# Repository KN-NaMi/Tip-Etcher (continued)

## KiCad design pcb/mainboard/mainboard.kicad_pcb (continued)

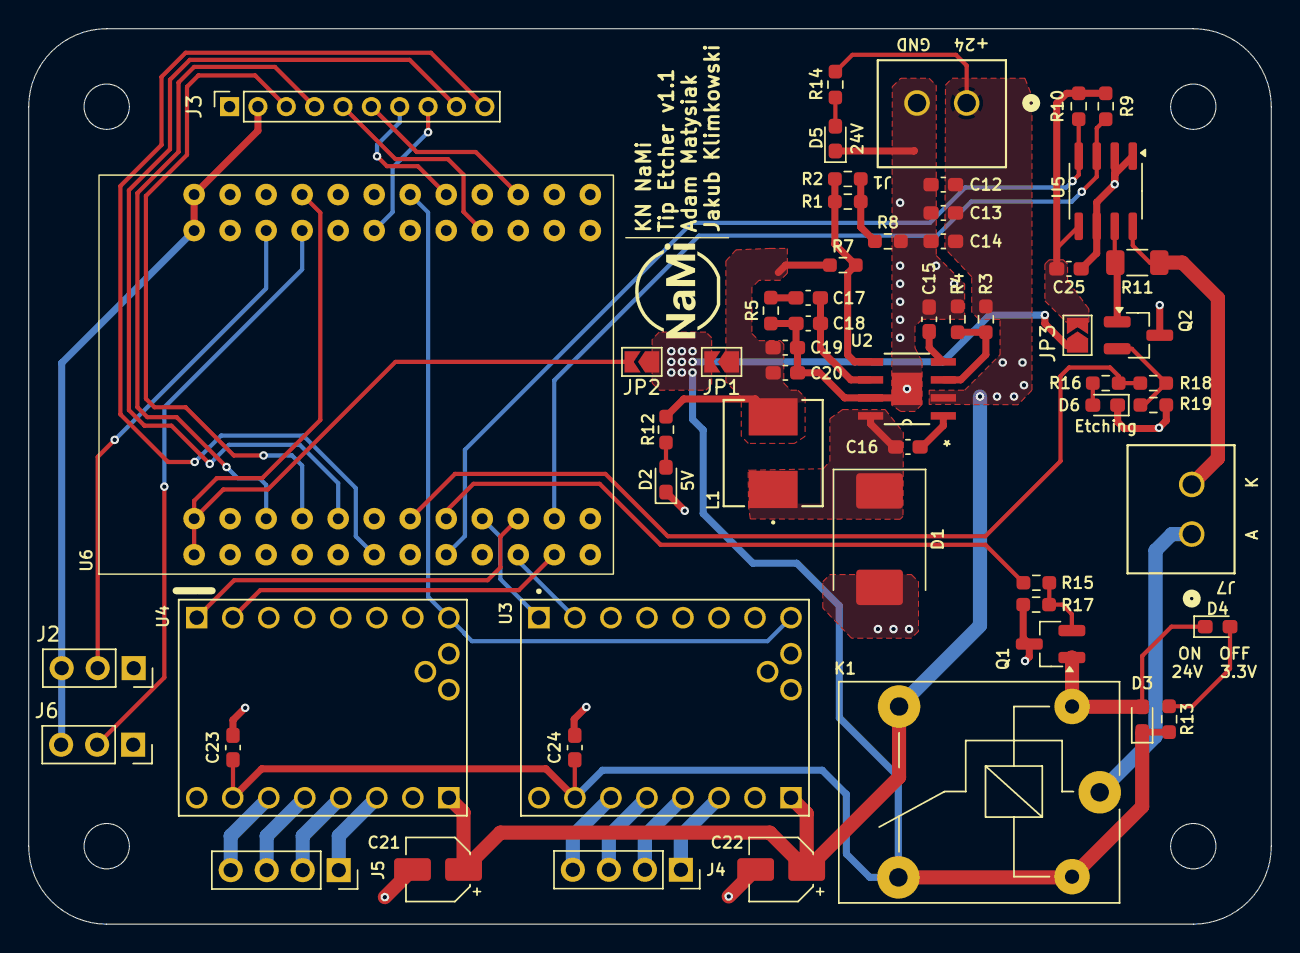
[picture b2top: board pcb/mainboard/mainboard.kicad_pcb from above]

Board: 2 copper layers, 87.6 x 63.1 mm, 61 parts (0 on the bottom side), 52 nets.

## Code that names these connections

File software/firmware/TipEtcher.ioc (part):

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Mcu.Name=STM32G474C(B-C-E)Ux
Mcu.Package=UFQFPN48
Mcu.UserName=STM32G474CEUx
PA0.GPIOParameters=GPIO_Label
PA0.GPIO_Label=OLED_RESET
PA0.Signal=GPIO_Output
PA1.GPIOParameters=GPIO_Label
PA1.GPIO_Label=OLED_DC
PA1.Signal=GPIO_Output
PA12.GPIOParameters=GPIO_Label
PA12.GPIO_Label=TIP_EN
PA12.Signal=GPIO_Output
PA15.Mode=I2C
PA15.Signal=I2C1_SCL
PA4.GPIOParameters=GPIO_Label
PA4.GPIO_Label=OLED_CS
PA4.Signal=GPIO_Output
PA6.GPIOParameters=GPIO_Label
PA6.GPIO_Label=M_ENABLE
PA6.Signal=GPIO_Output
PA7.GPIOParameters=GPIO_Label,GPIO_ModeDefaultEXTI
PA7.GPIO_Label=ENCODER_BTN
PA7.GPIO_ModeDefaultEXTI=GPIO_MODE_IT_FALLING
PA7.Signal=GPXTI7
PA8.GPIOParameters=GPIO_Label,GPIO_ModeDefaultEXTI
PA8.GPIO_Label=ENCODER_SIGA
PA8.GPIO_ModeDefaultEXTI=GPIO_MODE_IT_RISING_FALLING
PA8.Signal=GPXTI8
PA9.GPIOParameters=GPIO_Label
PA9.GPIO_Label=ENCODER_SIGB
PA9.Signal=GPIO_Input
PB10.GPIOParameters=GPIO_Label
PB10.GPIO_Label=LIMIT_SWITCH_1
PB10.Signal=GPIO_Input
PB13.GPIOParameters=GPIO_Label
PB13.GPIO_Label=OLED_SPI2_SCK
PB13.Mode=TX_Only_Simplex_Unidirect_Master
PB13.Signal=SPI2_SCK
PB15.GPIOParameters=GPIO_Label
PB15.GPIO_Label=OLED_SPI2_MOSI
PB15.Mode=TX_Only_Simplex_Unidirect_Master
PB15.Signal=SPI2_MOSI
PB3.GPIOParameters=GPIO_Label
PB3.GPIO_Label=DIR_1
PB3.Signal=GPIO_Output
PB4.GPIOParameters=GPIO_Label
PB4.GPIO_Label=STEP_1
PB4.Signal=GPIO_Output
PB5.GPIOParameters=GPIO_Label
PB5.GPIO_Label=DIR_2
PB5.Signal=GPIO_Output
PB6.GPIOParameters=GPIO_Label
PB6.GPIO_Label=STEP_2
PB6.Signal=GPIO_Output
PB7.Mode=I2C
PB7.Signal=I2C1_SDA
PC10.GPIOParameters=GPIO_Label
PC10.GPIO_Label=V_SELECT
PC10.Signal=GPIO_Output
PC13.GPIOParameters=GPIO_Label
PC13.GPIO_Label=BOARD_BTN
PC13.Signal=GPIO_Input
PC6.GPIOParameters=GPIO_Label
PC6.GPIO_Label=LED
PC6.Signal=GPIO_Output
RCC.HSE_VALUE=8000000
RCC.SYSCLKFreq_VALUE=16000000
board=custom

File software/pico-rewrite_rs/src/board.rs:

use embedded_hal::digital::OutputPin;

use crate::hal;

#[derive(Clone, Copy, Debug, Eq, PartialEq)]
#[repr(u8)]
pub enum GpioPin {
    Gpio0,
    Gpio1,
    Gpio2,
    Gpio3,
    Gpio4,
    Gpio5,
    Gpio6,
    Gpio7,
    Gpio8,
    Gpio9,
    Gpio10,
    Gpio11,
    Gpio12,
    Gpio13,
    Gpio14,
    Gpio15,
    Gpio16,
    Gpio17,
    Gpio18,
    Gpio19,
    Gpio20,
    Gpio21,
    Gpio22,
    Gpio23,
    Gpio24,
    Gpio25,
    Gpio26,
    Gpio27,
    Gpio28,
    Gpio29,
}

#[derive(Clone, Copy, Debug, Default)]
pub struct PinMap {
    pub board_button: Option<GpioPin>,
    pub oled_reset: Option<GpioPin>,
    pub oled_data_command: Option<GpioPin>,
    pub oled_chip_select: Option<GpioPin>,
    pub motor_enable: Option<GpioPin>,
    pub encoder_button: Option<GpioPin>,
    pub limit_switch_1: Option<GpioPin>,
    pub oled_spi_clock: Option<GpioPin>,
    pub oled_spi_data: Option<GpioPin>,
    pub status_led: Option<GpioPin>,
    pub encoder_a: Option<GpioPin>,
    pub encoder_b: Option<GpioPin>,
    pub tip_enable: Option<GpioPin>,
    pub voltage_select: Option<GpioPin>,
    pub motor_1_direction: Option<GpioPin>,
    pub motor_1_step: Option<GpioPin>,
    pub motor_2_direction: Option<GpioPin>,
    pub motor_2_step: Option<GpioPin>,
    pub current_sensor_i2c_clock: Option<GpioPin>,
    pub current_sensor_i2c_data: Option<GpioPin>,
}

// Assign RP GPIOs here after the target Pico board and pinout are chosen.
pub const PIN_MAP: PinMap = PinMap {
    board_button: None,
    oled_reset: None,
    oled_data_command: None,
    oled_chip_select: None,
    motor_enable: None,
    encoder_button: None,
    limit_switch_1: None,
    oled_spi_clock: None,
    oled_spi_data: None,
    status_led: None,
    encoder_a: None,
    encoder_b: None,
    tip_enable: None,
    voltage_select: None,
    motor_1_direction: None,
    motor_1_step: None,
    motor_2_direction: None,
    motor_2_step: None,
    current_sensor_i2c_clock: None,
    current_sensor_i2c_data: None,
};

pub struct BlinkyPins<LedPin> {
    pub led: LedPin,
}


//OLED: CS(port, pin), DC(port, pin), RESET(port, pin), 
//ENCODER: SIGA(port, pin), SIGB(port, pin), BTN(port, pin) 
pub struct MENU; 

pub fn configure_blinky(pins: hal::gpio::Pins) -> BlinkyPins<impl OutputPin> {
    BlinkyPins {
        led: pins.gpio25.into_push_pull_output(),
    }
}

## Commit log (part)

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2025-02-09 init
2025-02-09 update license
2025-02-09 add CODEOWNERS
2025-02-10 add corner bracker
2025-02-12 add L-mount
2025-02-24 add frame assembly
2025-02-25 add stm with voltage converte
2025-02-28 Add USB C port and integrate it with uC
2025-03-03 add psu-mount
2025-03-30 add stepsticks
2025-03-30 add IDA
2025-03-30 Add TIP Voltage Control
2025-03-31 Create pcb
2025-04-11 fix assembly
2025-07-07 Minor Schematic & Major PCB Rework
2025-07-08 Update PCB
2025-07-08 Update PCB Change Buck Converter Vout from 3.3V to 5V
2025-07-09 Update PCB | Requested Changes
2025-07-09 Change OLED Connector Size
    Changed size of an OLED connector from 2.54mm to 2.00mm to match its size from other related project.
2025-07-24 Add Limit Switches
2025-07-24 Change Limit Switch Connectors
    Change from 2 pin to 3 pin connectors
2025-09-04 Assembly
    Wszystkie elementy drukowane są już zawarte. Pozostało uzupełnienie o łożyska itp.
2025-11-09 standarize repo
2025-12-21 Add Code
    Still have some bugs, however was tested and device is etching properly
2026-02-26 Update software
2026-03-14 New PCB version
2026-03-19 Tip Etcher V 2.0
    Zaktualizowany model 3D
2026-04-25 Frame - initial
2026-04-25 Base - no holes
2026-04-25 Base
2026-05-05 Base + top_bracket
2026-05-06 Base + top_bracket rev2
2026-05-13 Electronic Box
    Poprawić tolerancję ścian w szczególności pomiędzy head'em , a boxem
2026-06-09 Brakuje tylko jack'a i sprawdzenia
